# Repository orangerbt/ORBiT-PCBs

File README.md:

# ORBiT Avionics

Schematics and PCBS for ORBiT Avionics system.

## Modules

- Telemetry (GPS, IMU, atmospheric conditions, remote control)
    - Digi 9Xtend 900MHz 1W radio
    - Linx TM series GNSS reciever
    - Bosch BMX055 IMU
    - Bosch BME280 atmospheric conditions sensor
- Power (battery management, charging, regulation)
    - TI bq40z60 BMU
    - TI TPS40305 5V regulator
- Actuation (power devices)
    - 3x Microchip MCP23008 I2C I/O expanders
    - 2x Microchip MCP33926 H-bridge drivers
- Data acquisition (sensors)
    - Analog Devices AD9201 ADC
    - Analog Devices LTC2984 temperature measurement system

## Notes
- Make sure to power down HDMI framer via I2C0
- Add CAT24C256 EEPROMs to identify modules via I2C2
- Ensure I2C pins have pull-ups
- Add power sequencing to all boards
- Data acquisition to be based on PRUDAQ
- Add LTC2983/4/6 and LTC6904 to DAQ
- Test points

## Hardware pin mapping

### Telemetry

- UART4 - P8 33 uart4_rtsn, 35 uart4_ctsn, P9 11 uart4_rxd, 13 uart4_txd
- UART5 - P8 37 uart5_txd, 38 uart5_rxd
- SPI0  - P8 26-28, P9 17 spi0_cs0, 18 spi0_d1, 21 spi0_d0, 22 spi0_sclk
    - SPI0 addressing
    - P8 26 gpio61 = A0
    - P8 27 gpio86 = A1
    - P8 28 gpio88 = A2
- I2C1  - P9 24 I2C1_SCL, 26 I2C1_SDA
- I2C2  - P9 19 I2C2_SCL, 22 I2C2_SDA

### Power management

- I2C1 - P9 24 I2C1_SCL, 26 I2C1_SDA

### Actuator control

- I2C1 - P9 24 I2C1_SCL, 26 I2C1_SDA
- GPIO - P9 25, 27, 28

### PRUDAQ:
- P8 27-30, 39-46
- P9 25-31

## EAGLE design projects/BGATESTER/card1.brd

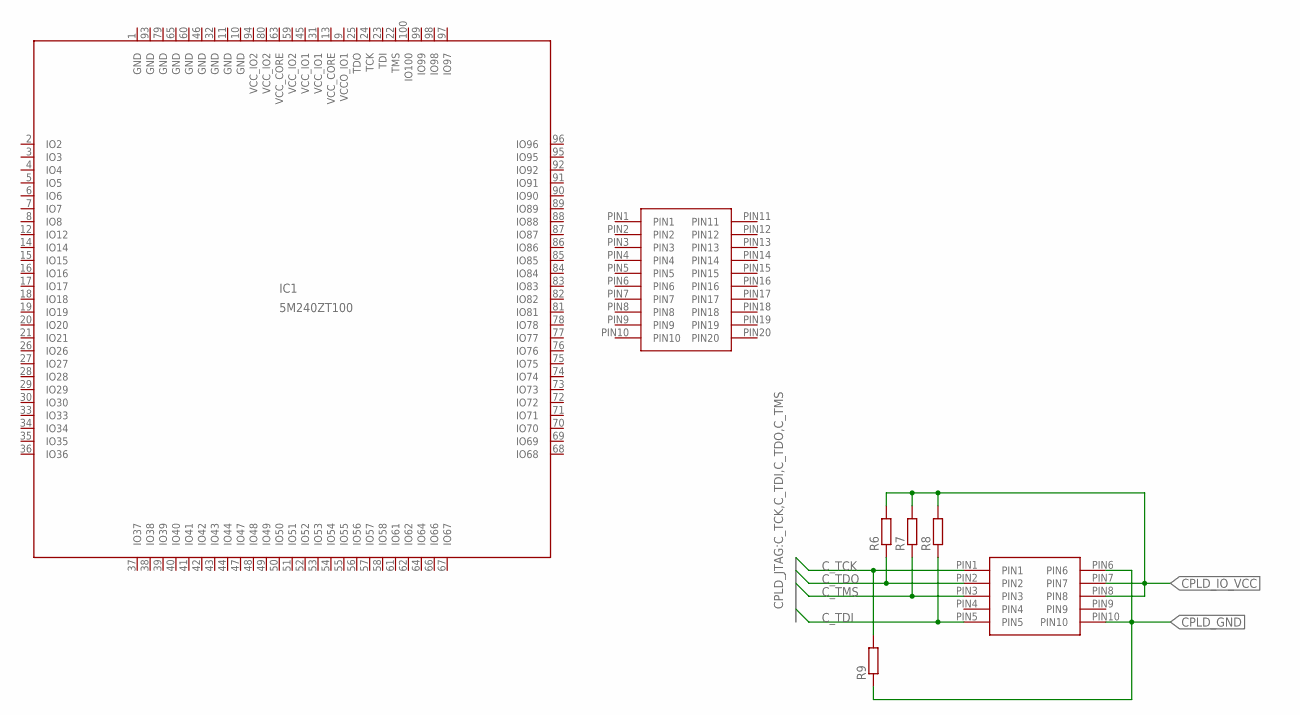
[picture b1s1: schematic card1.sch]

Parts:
IC1: 5M240ZT100; TQFP100
R6, R7, R8, R9: R-EU_R2012; R2012
U$1: 10PIN10PIN_BOARD; 10PIN_BOARD
U$3: CONN-10PINR/A-10PIN; R/A-10PIN

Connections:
CPLD_GND: R9.1, U$3.PIN6, U$3.PIN10
CPLD_IO_VCC: R6.2, R7.2, R8.2, U$3.PIN7, U$3.PIN8
C_TCK: R9.2, U$3.PIN1
C_TDI: R8.1, U$3.PIN5
C_TDO: R6.1, U$3.PIN2
C_TMS: R7.1, U$3.PIN3
GND: IC1.1 (GND), IC1.10 (GND), IC1.11 (GND), IC1.32 (GND), IC1.46 (GND), IC1.60 (GND), IC1.65 (GND), IC1.79 (GND), IC1.93 (GND)
VCCO_IO1: IC1.9 (VCCO_IO1)
VCC_CORE: IC1.13 (VCC_CORE), IC1.63 (VCC_CORE)
VCC_IO1: IC1.31 (VCC_IO1), IC1.45 (VCC_IO1)
VCC_IO2: IC1.59 (VCC_IO2), IC1.80 (VCC_IO2), IC1.94 (VCC_IO2)

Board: 2 copper layers, 7 parts (0 on the bottom side), 10 nets, no tracks yet.

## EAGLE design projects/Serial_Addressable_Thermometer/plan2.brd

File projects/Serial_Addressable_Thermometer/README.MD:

# Serial Addressable Thermometer
## Plan 3
- Use PIC micro controller with AD, use I2C as communication
- Adventage: faster, build in assembly
- Disadventage: Hard to upgrade
## Part List
    1. FPC connector
       1. 68611014422
       2. https://www.digikey.com/product-detail/en/wurth-electronics-inc/68611014422/732-1996-1-ND/2060620
       3. AFFC-100-10-051-11
       4. https://www.digikey.com/product-detail/en/assmann-wsw-components/AFFC-100-10-051-11/AE11354-ND/6570435
    2. NTC resistor 0805
       1. B57471V2103J062
       2. https://www.digikey.com/product-detail/en/epcos-tdk/B57471V2103J062/495-7449-1-ND/6073141
    3. 10K resistor 0805
       1. RMCF0805JT10K0
       2. https://www.digikey.com/product-detail/en/stackpole-electronics-inc/RMCF0805JT10K0/RMCF0805JT10K0CT-ND/1942577
    4. CAP CER 47UF 6.3V X5R 0805
       1. JMK212BBJ476MG-T
       2. https://www.digikey.com/product-detail/en/taiyo-yuden/JMK212BBJ476MG-T/587-4280-1-ND/5344315
    5. PIC16F18424-I/ST-ND
       1. A/D 11x12b; D/A 1x5b
       2. https://www.digikey.com/product-detail/en/microchip-technology/PIC16F18424-I-ST/PIC16F18424-I-ST-ND/8639243
    6. S4B-ZR-SM4A-TF(LF)(SN)
       1. CONN HEADER SMD R/A 4POS 1.5MM
       2. https://www.digikey.com/product-detail/en/jst-sales-america-inc/S4B-ZR-SM4A-TF-LF-SN/455-1695-1-ND/926822
    7. CONN SOCKET 26-28AWG CRIMP TIN
       1. https://www.digikey.com/product-detail/en/jst-sales-america-inc/SZH-002T-P0.5/455-1130-1-ND/527362
    8. CONN HOUSING ZH 4POS 1.5MM WHT
       1. https://www.digikey.com/product-detail/en/jst-sales-america-inc/ZHR-4/455-1202-ND/608643
    9. CONN HEADER SMD R/A 6POS 1.5MM
       1.  https://www.digikey.com/product-detail/en/jst-sales-america-inc/S6B-ZR-SM4A-TF-LF-SN/455-1610-1-ND/858041
    10. CONN HOUSING ZH 6POS 1.5MM	COPY 
        1.  https://www.digikey.com/product-detail/en/jst-sales-america-inc/ZHR-6/455-1129-ND/527361

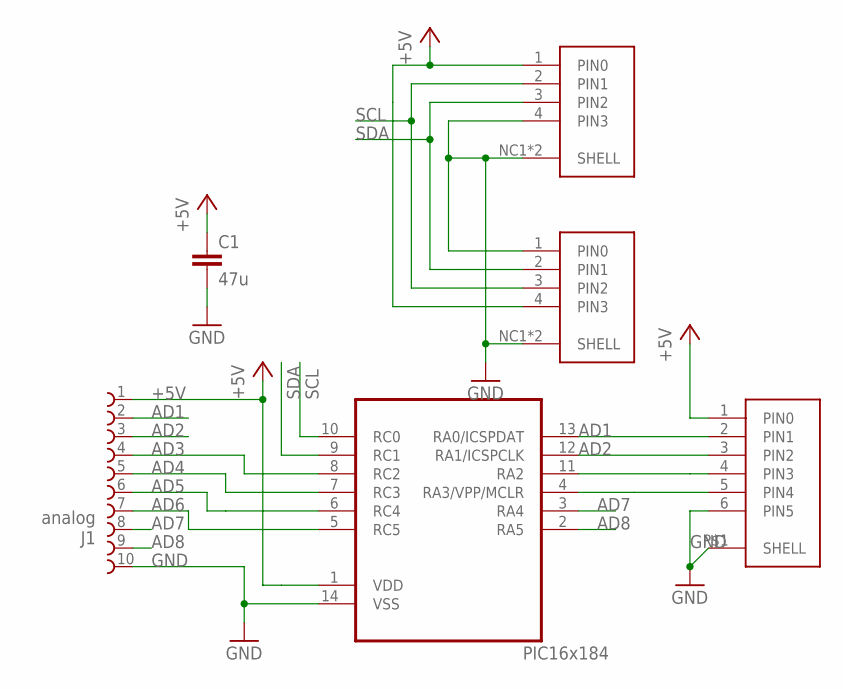
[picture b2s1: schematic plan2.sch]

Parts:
C1: 47u; C0805
J1: analog; 68611014422
MAINCON: PIC16F18424; 14-TSSOP
U$2: IIC1; JST_ZH_4PIN
U$3: IIC2; JST_ZH_4PIN
U$4: programming; JST_ZH_6PIN

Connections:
+5V: C1.1, J1.1 (10), MAINCON.1 (VDD), U$2.1 (PIN0), U$3.4 (PIN3), U$4.1 (PIN0)
AD1: J1.2 (9), MAINCON.13 (RA0/ICSPDAT), U$4.2 (PIN1)
AD2: J1.3 (8), MAINCON.12 (RA1/ICSPCLK), U$4.3 (PIN2)
AD3: J1.4 (7), MAINCON.8 (RC2)
AD4: J1.5 (6), MAINCON.7 (RC3)
AD5: J1.6 (5), MAINCON.6 (RC4)
AD6: J1.7 (4), MAINCON.5 (RC5)
AD7: J1.8 (3), MAINCON.3 (RA4)
AD8: J1.9 (2), MAINCON.2 (RA5)
GND: C1.2, J1.10 (1), MAINCON.14 (VSS), U$2.4 (PIN3), U$2.NC1 (SHELL), U$2.NC2 (SHELL), U$3.1 (PIN0), U$3.NC1 (SHELL), U$3.NC2 (SHELL), U$4.6 (PIN5), U$4.P$1 (SHELL)
unnamed: MAINCON.11 (RA2), U$4.4 (PIN3)
unnamed: MAINCON.4 (RA3/VPP/MCLR), U$4.5 (PIN4)
SCL: MAINCON.10 (RC0), U$2.2 (PIN1), U$3.3 (PIN2)
SDA: MAINCON.9 (RC1), U$2.3 (PIN2), U$3.2 (PIN1)

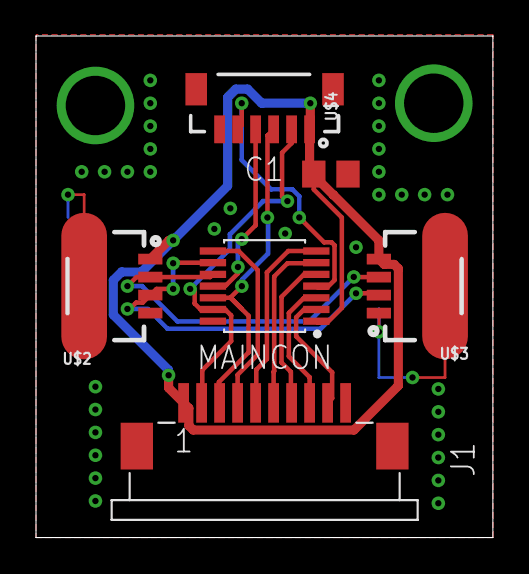
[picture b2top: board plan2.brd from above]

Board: 2 copper layers, 25.4 x 27.9 mm, 6 parts (0 on the bottom side), 14 nets.

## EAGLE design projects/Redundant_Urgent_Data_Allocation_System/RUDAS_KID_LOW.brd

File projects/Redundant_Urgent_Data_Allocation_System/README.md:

# Chip Selection
1.  Low-end board Chip
    1.  STM32F103VGT6
        1.  https://www.digikey.com/product-detail/en/stmicroelectronics/STM32F103VGT6/497-11120-ND/2529309
2.  High-end board Chip
    1.  STM32F412VET6
        1.  https://www.digikey.com/product-detail/en/stmicroelectronics/STM32F412VET6/497-17837-ND/6621744
3.  Dual Port SRAM
    1.  71V30S55TFG
        1.  https://www.digikey.com/product-detail/en/idt-integrated-device-technology-inc/71V30S55TFG/800-3622-ND/4400847
4.  CPLD
    1.  5M240ZT100C5N
        1.  https://www.digikey.com/product-detail/en/intel/5M240ZT100C5N/544-2716-ND/2499439
5.  CAN Driver
    1.  ISO1050
    2.  https://www.digikey.com/product-detail/en/texas-instruments/ISO1050DUBR/296-24818-1-ND/2094658
6.  Voltage Regulator
    1.  AP1501A-12K5G-13
        1.  https://www.digikey.com/product-detail/en/diodes-incorporated/AP1501A-12K5G-13/AP1501A-12K5G-13DIDKR-ND/8546155
    2.  LM2679SX-3.3/NOPB
        1.  https://www.digikey.com/product-detail/en/texas-instruments/LM2679SX-3.3-NOPB/LM2679SX-3.3-NOPBCT-ND/3526908
    3.  AP1509-50SG-13
        1.  https://www.digikey.com/product-detail/en/diodes-incorporated/AP1509-50SG-13/AP1509-50SGDICT-ND/1301653

# Connector
1. JTAG
   1. 3M 2500
      1. 20 Pin
         1. https://www.digikey.com/product-detail/en/3m/N2520-6002-RB/MHC20K-ND/755179
         2. https://www.digikey.com/product-detail/en/3m/N2520-5002-RB/MHE20K-ND/755191
         3. https://www.digikey.com/product-detail/en/3m/N2520-6V0C-RB-WE/MSH20KCT-ND/1125449
2. FPC
   1. Wurth Electronics Inc. WR-FPC
      1. https://www.digikey.com/products/en/connectors-interconnects/ffc-fpc-flat-flexible-connectors/399?k=&pkeyword=&sv=0&sf=0&FV=ffe0018f%2Cfffc02dc&quantity=1&ColumnSort=0&page=1&stock=1&datasheet=1&photo=1&pageSize=25

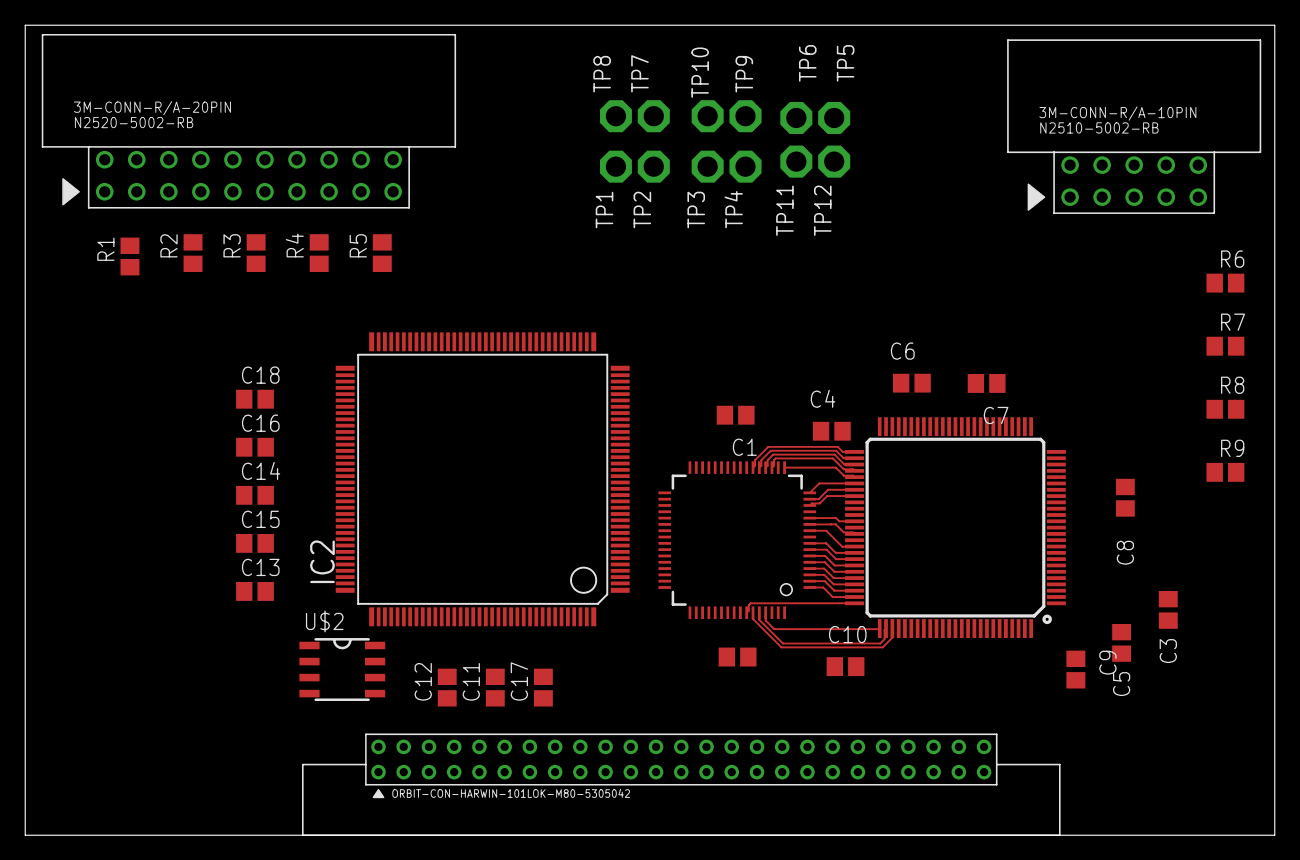
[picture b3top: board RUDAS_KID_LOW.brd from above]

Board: 4 copper layers, 99.0 x 64.2 mm, 46 parts (0 on the bottom side), 102 nets.

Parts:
C1, C2, C3, C4, C5, C6, C7, C8, C9, C10, C11, C12, C13, C14, C15, C16, C17, C18: C2012
IC2: STM32F103VGT6; LQFP144
IC3: 5M240ZT100; TQFP100
R1, R2, R3, R4, R5, R6, R7, R8, R9: R2012
TP1, TP2, TP3, TP4, TP5, TP6, TP7, TP8, TP9, TP10, TP11, TP12: TP063; TP_063
U$1: IDT71V30; TQFP64
U$2: ISO1050; SOP8
U$3: CONN-10PINR/A-10PIN; R/A-10PIN
U$4: CONN-20PINR/A-20PIN; R/A-20PIN
U$5: CARD_EDGE_50PINM80-5305042; M80-5305042

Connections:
!BUSY!: IC3.77, U$1.60
!CE!: IC3.75, U$1.58
!INT!: IC3.76, U$1.61
!OE!: IC3.74, U$1.1
A0: IC3.73, U$1.2
A1: IC3.72, U$1.3
A2: IC3.71, U$1.4
A3: IC3.70, U$1.5
A4: IC3.69, U$1.6
A5: IC3.68, U$1.7
A6: IC3.67, U$1.8
A7: IC3.66, U$1.10
A8: IC3.64, U$1.11
A9: IC3.62, U$1.12
CAN_H_P: U$2.7, U$5.PIN4
CAN_L_P: U$2.6, U$5.PIN5
CPLD_GND: C3.2, C4.2, C5.2, C6.2, C7.2, C8.2, C9.2, C10.2, IC3.1, IC3.10, IC3.11, IC3.32, IC3.46, IC3.60, IC3.65, IC3.79, IC3.93, R9.1, U$3.PIN6, U$3.PIN10
CPLD_IO_VCC: R6.2, R7.2, R8.2, U$3.PIN7, U$3.PIN8
CPLD_VCC: C3.1, C4.1, C5.1, C6.1, C7.1, C8.1, C9.1, C10.1
CPLD_VCC_CORE: IC3.13, IC3.63
CPLD_VCC_IO2: IC3.59, IC3.80, IC3.94
CPL_VCC_IO1: IC3.9, IC3.31, IC3.45
C_TCK: IC3.24, R9.2, U$3.PIN1
C_TDI: IC3.23, R8.1, U$3.PIN5
C_TDO: IC3.25, R6.1, U$3.PIN2
C_TMS: IC3.22, R7.1, U$3.PIN3
D0: IC3.58, U$1.14
D1: IC3.57, U$1.15
D2: IC3.56, U$1.16
D3: IC3.55, U$1.17
D4: IC3.54, U$1.19
D5: IC3.53, U$1.20
D6: IC3.52, U$1.21
D7: IC3.51, U$1.22
FSMC_!NE1!: IC2.123, U$1.55
FSMC_!NOE!: IC2.118, U$1.48
FSMC_A0: IC2.10, U$1.47
FSMC_A1: IC2.11, U$1.46
FSMC_A2: IC2.12, U$1.45
FSMC_A3: IC2.13, U$1.44
FSMC_A4: IC2.14, U$1.43
FSMC_A5: IC2.15, U$1.42
FSMC_A6: IC2.50, U$1.41
FSMC_A7: IC2.53, U$1.39
FSMC_A8: IC2.54, U$1.38
FSMC_A9: IC2.55, U$1.37
FSMC_D0: IC2.85, U$1.26
FSMC_D1: IC2.86, U$1.27
FSMC_D2: IC2.114, U$1.28
FSMC_D3: IC2.115, U$1.29
FSMC_D4: IC2.58, U$1.31
FSMC_D5: IC2.59, U$1.32
FSMC_D6: IC2.60, U$1.33
FSMC_D7: IC2.63, U$1.34
LAN_CLK_N0: IC3.81, U$5.PIN9
LAN_CLK_N1: IC3.85, U$5.PIN15
LAN_CLK_N2: IC3.96, U$5.PIN21
LAN_CLK_N3: IC3.29, U$5.PIN34
LAN_CLK_N4: IC3.19, U$5.PIN40
LAN_CLK_N5: IC3.5, U$5.PIN46
LAN_CLK_P0: IC3.82, U$5.PIN10
LAN_CLK_P1: IC3.86, U$5.PIN16
LAN_CLK_P2: IC3.97, U$5.PIN22
LAN_CLK_P3: IC3.28, U$5.PIN35
LAN_CLK_P4: IC3.18, U$5.PIN41
LAN_CLK_P5: IC3.4, U$5.PIN47
LAN_N0: IC3.83, U$5.PIN11
LAN_N1: IC3.87, U$5.PIN17
LAN_N2: IC3.98, U$5.PIN23
LAN_N3: IC3.27, U$5.PIN36
LAN_N4: IC3.17, U$5.PIN42
LAN_N5: IC3.3, U$5.PIN48
LAN_P0: IC3.84, U$5.PIN12
LAN_P1: IC3.88, U$5.PIN18
LAN_P2: IC3.99, U$5.PIN24
LAN_P3: IC3.26, U$5.PIN37
LAN_P4: IC3.16, U$5.PIN43
LAN_P5: IC3.2, U$5.PIN49
unnamed: C1.1, C2.1, U$1.56, U$1.57
unnamed: C1.2, C2.2, U$1.24, U$1.25
R/!W!: IC3.78, U$1.59
SIGNAL_GND: U$2.5, U$5.PIN8, U$5.PIN14, U$5.PIN20, U$5.PIN33, U$5.PIN39, U$5.PIN45
STM32_CAN_RX: IC2.103, TP7.TP, U$2.2
STM32_CAN_TX: IC2.104, TP8.TP, U$2.3
STM32_I2C1_SCL: IC2.136, TP9.TP
STM32_I2C1_SDA: IC2.137, TP10.TP
STM32_SPI1_CS: IC2.40, TP1.TP
STM32_SPI1_MISO: IC2.42, TP3.TP
STM32_SPI1_MOSI: IC2.43, TP4.TP
STM32_SPI1_SCK: IC2.41, TP2.TP
STM32_UART1_RX: IC2.102, TP6.TP
STM32_UART1_TX: IC2.101, TP5.TP
STM32_UART2_RX: IC2.36, TP12.TP
STM32_UART2_TX: IC2.35, TP11.TP
S_GND: C11.2, C12.2, C13.2, C14.2, C15.2, C16.2, C17.2, C18.2, IC2.16, IC2.38, IC2.51, IC2.61, IC2.71, IC2.83, IC2.94, IC2.107, IC2.120, IC2.130, IC2.143, R5.1, U$2.4, U$4.PIN12, U$4.PIN13, U$4.PIN14, U$4.PIN15, U$4.PIN16, U$4.PIN17, U$4.PIN18, U$4.PIN19, U$4.PIN20
S_RST: IC2.25, U$4.PIN9
S_TCK: IC2.109, R5.2, U$4.PIN5
S_TDI: IC2.110, R2.1, U$4.PIN3
S_TDO: IC2.133, R4.1, U$4.PIN7
S_TMS: IC2.105, R3.1, U$4.PIN4
S_TRST: IC2.134, R1.1, U$4.PIN2
S_VCC: C11.1, C12.1, C13.1, C14.1, C15.1, C16.1, C17.1, C18.1, IC2.17, IC2.39, IC2.52, IC2.62, IC2.72, IC2.84, IC2.95, IC2.108, IC2.121, IC2.131, IC2.144, R1.2, R2.2, R3.2, R4.2, U$2.1, U$4.PIN1, U$4.PIN11

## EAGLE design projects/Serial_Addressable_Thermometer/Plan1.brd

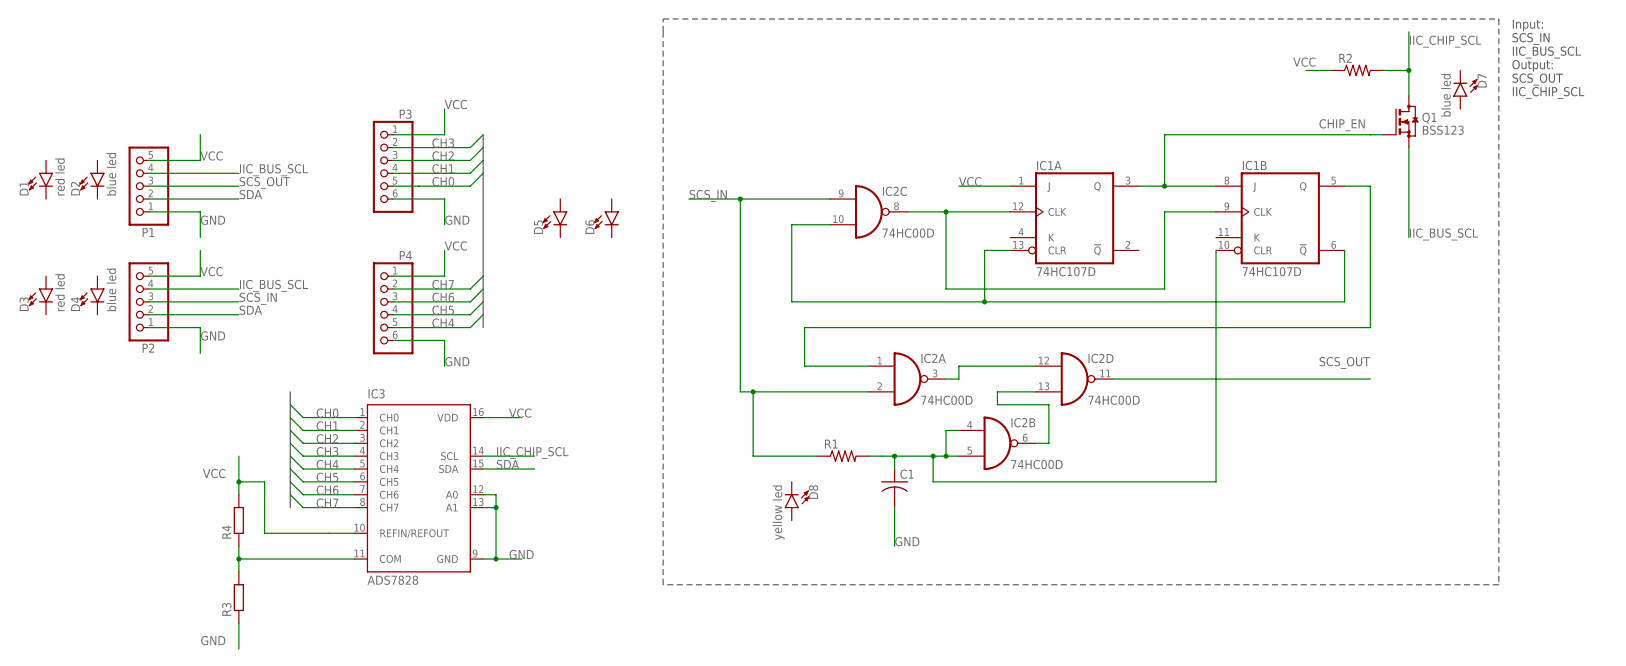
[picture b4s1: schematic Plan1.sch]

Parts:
C1: C-USC1206; C1206
D1, D3: red led; LED-0603
D2, D4, D7: blue led; LED-0603
D5, D6: LED0603; LED-0603
D8: yellow led; LED-0603
IC1: 74HC107D; SO14
IC2: 74HC00D; SO14
IC3: ADS7828; TSSOP16-PW
P1, P2: 105313-05; 105313-**05
P3, P4: 105313-06; 105313-**06
Q1: BSS123; SOT23
R1, R2: R-US_R1206; R1206
R3, R4: R-EU_R2012; R2012

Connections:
CH0: IC3.1 (CH0), P3.5
CH1: IC3.2 (CH1), P3.4
CH2: IC3.3 (CH2), P3.3
CH3: IC3.4 (CH3), P3.2
CH4: IC3.5 (CH4), P4.5
CH5: IC3.6 (CH5), P4.4
CH6: IC3.7 (CH6), P4.3
CH7: IC3.8 (CH7), P4.2
CHIP_EN: IC1.3 (Q), IC1.8 (J), Q1.1 (G)
GND: C1.2, IC1.7 (GND), IC2.7 (GND), IC3.9 (GND), IC3.12 (A0), IC3.13 (A1), P1.1, P2.1, P3.6, P4.6, R3.1
IIC_BUS_SCL: P1.4, P2.4, Q1.2 (S)
IIC_CHIP_SCL: IC3.14 (SCL), Q1.3 (D), R2.2
unnamed: IC1.9 (CLK), IC1.12 (CLK), IC2.8 (O)
unnamed: C1.1, IC1.10 (CLR), IC2.4 (I0), IC2.5 (I1), R1.2
unnamed: IC2.6 (O), IC2.13 (I1)
unnamed: IC1.6 (!Q), IC1.13 (CLR), IC2.10 (I1)
unnamed: IC1.5 (Q), IC2.1 (I0)
unnamed: IC2.3 (O), IC2.12 (I0)
unnamed: IC3.11 (COM), R3.2, R4.1
SCS_IN: IC2.2 (I1), IC2.9 (I0), P2.3, R1.1
SCS_OUT: IC2.11 (O), P1.3
SDA: IC3.15 (SDA), P1.2, P2.2
VCC: IC1.1 (J), IC1.14 (VCC), IC2.14 (VCC), IC3.10 (REFIN/REFOUT), IC3.16 (VDD), P1.5, P2.5, P3.1, P4.1, R2.1, R4.2

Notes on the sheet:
Input: SCS_IN IIC_BUS_SCL Output: SCS_OUT IIC_CHIP_SCL

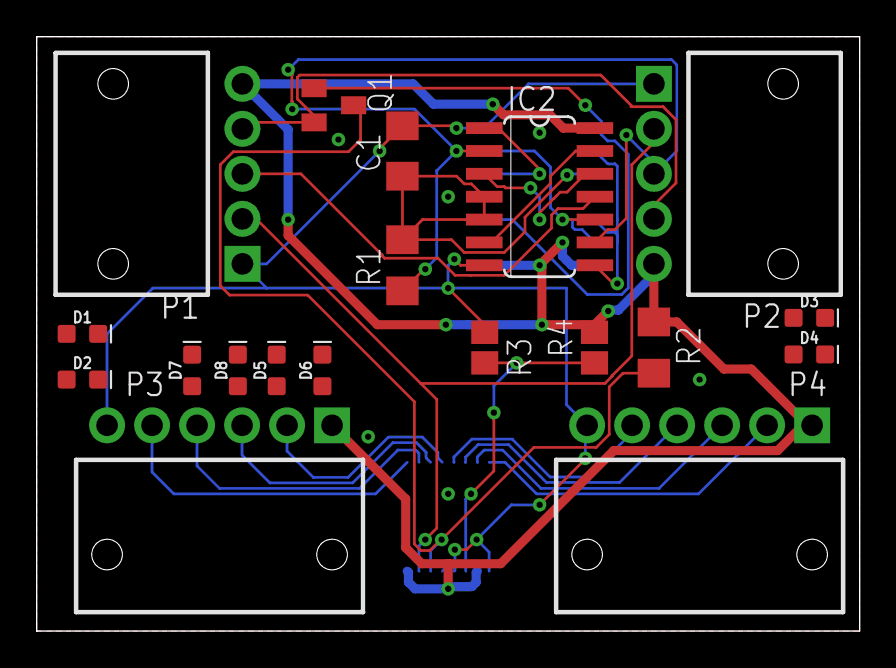
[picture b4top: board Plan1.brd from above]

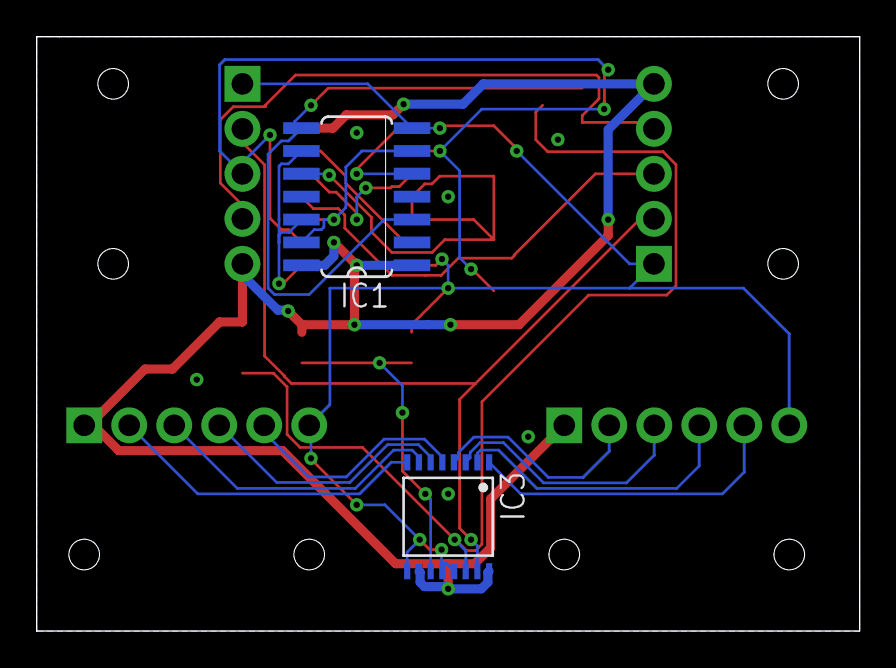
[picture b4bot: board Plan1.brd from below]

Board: 2 copper layers, 45.7 x 33.0 mm, 21 parts (2 on the bottom side), 23 nets.

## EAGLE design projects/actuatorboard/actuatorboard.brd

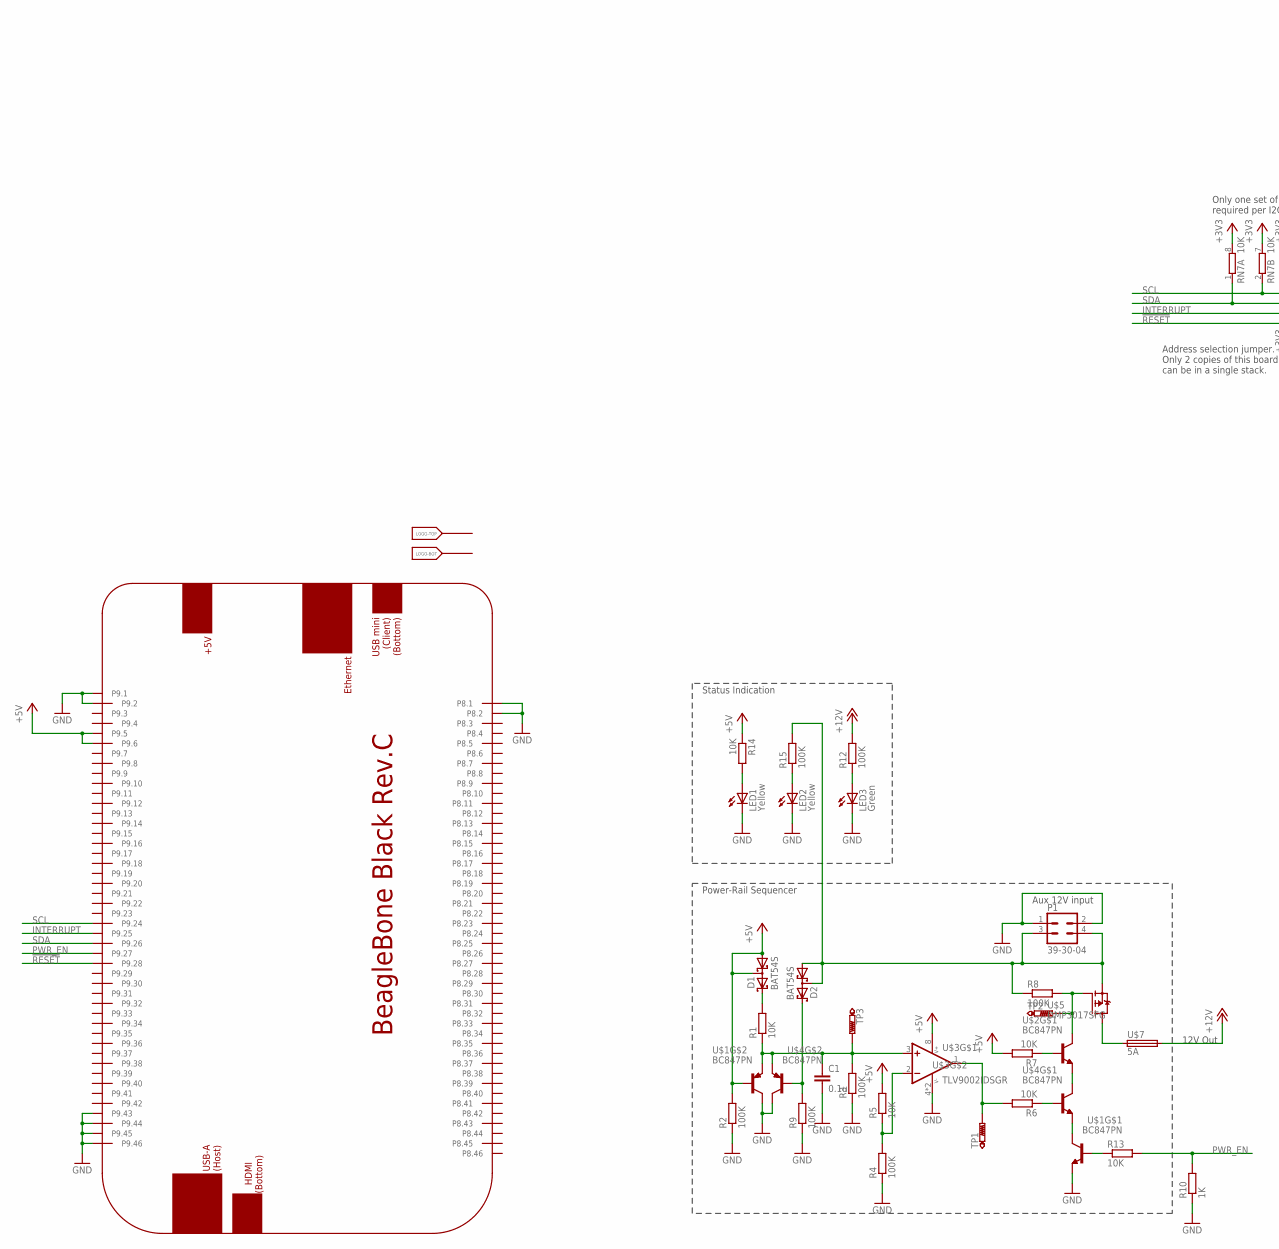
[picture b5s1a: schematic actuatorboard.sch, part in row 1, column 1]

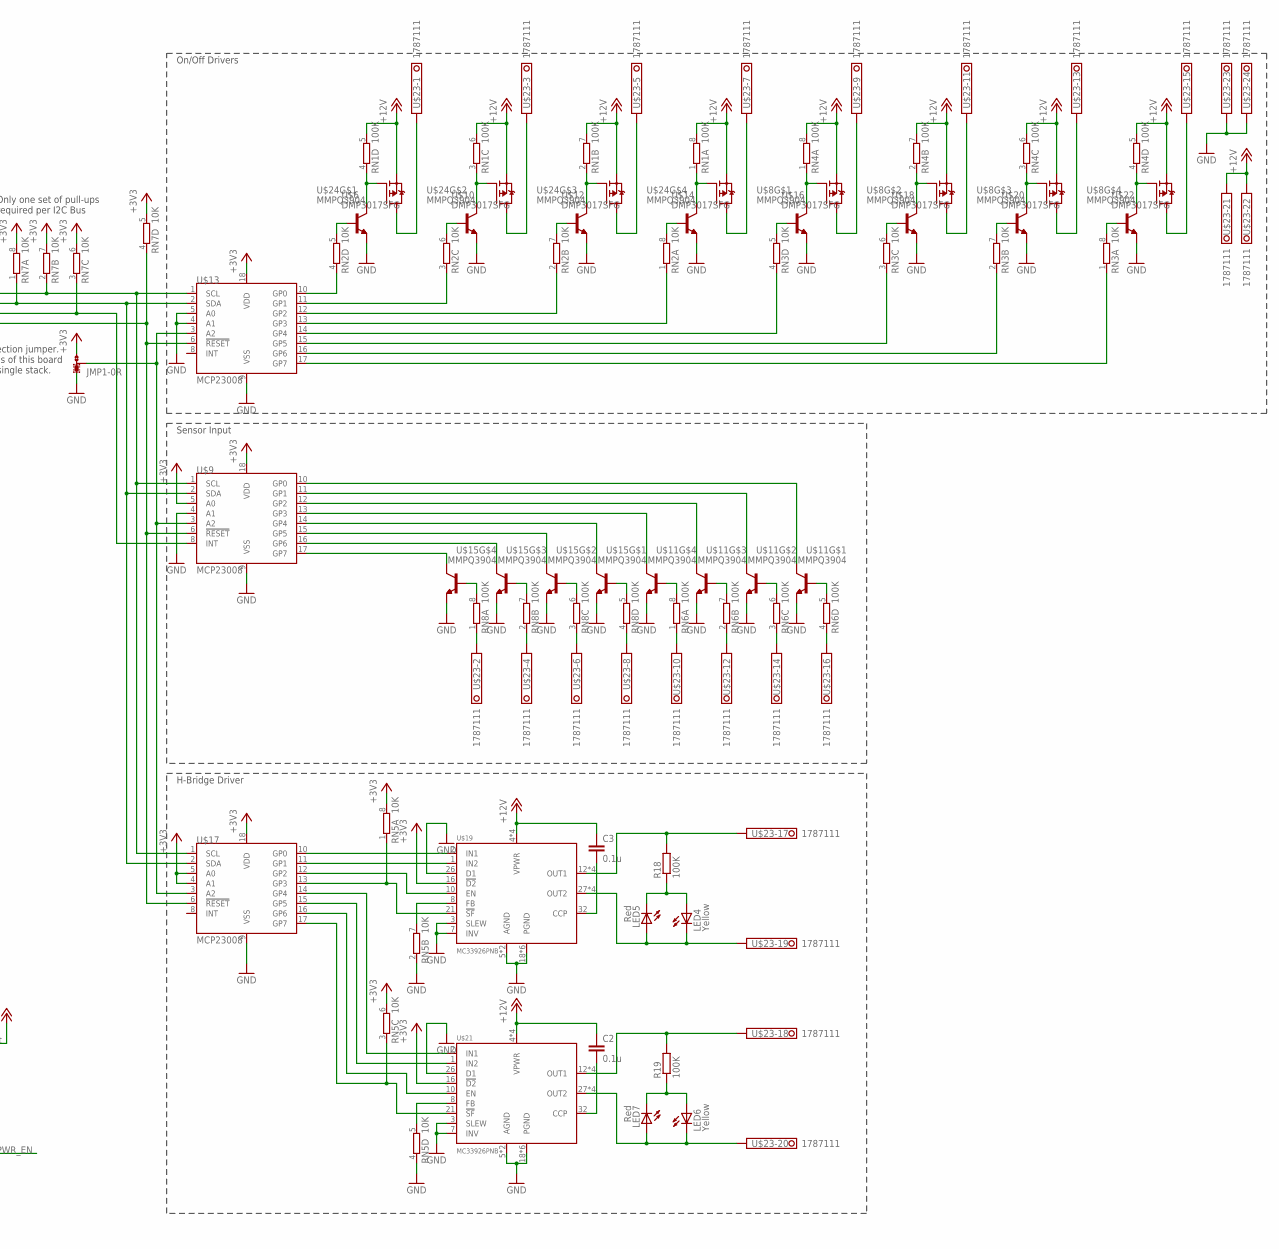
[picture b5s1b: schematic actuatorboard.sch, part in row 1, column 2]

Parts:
C1, C2, C3: 0.1u; C0805
D1, D2: BAT54S; SOT23
JMP1: 0R-JUMPA; A0R-JMP
LED1, LED2, LED4, LED6: Yellow; CHIPLED_0805
LED3: Green; CHIPLED_0805
LED5, LED7: Red; CHIPLED_0805
LOGO: SU_LOGO-DUMMY; SU_LOGO_DS
P1: 39-30-04; 39-30-?04?
PCB1: BEAGLEBONE_BLACK_CAPENO_ETH; BEAGLEBONE_BLACK_CAPE_NO_ETH
R1, R5, R6, R7, R13, R14: 10K; R0805
R2, R3, R4, R8, R9, R12, R15, R18, R19: 100K; R0805
R10: 1K; R0805
RN1, RN4, RN6, RN8: 100K; EXBV8V
RN2, RN3, RN5, RN7: 10K; EXBV8V
TP1, TP2, TP3: PTR1B1,27; B1,27
U$1, U$2, U$4: BC847PN; SOT363-INFINION
U$3: TLV9002IDSGR; S-PWSON-N8
U$5, U$6, U$10, U$12, U$14, U$16, U$18, U$20, U$22: DMP3017SFG; POWERDI3333-8
U$7: 5A; SMD-1206
U$8, U$11, U$15, U$24: MMPQ3904; SOIC-16
U$9, U$13, U$17: MCP23008; SO-18W
U$19, U$21: MC33926PNB; PQFN-32
U$23: 1787111

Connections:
!RESET!: PCB1.P9.28, RN7.4 (1), U$9.6 (!RESET!), U$13.6 (!RESET!), U$17.6 (!RESET!)
+3V3: JMP1.3, RN5.6 (2), RN5.8 (2), RN7.5 (2), RN7.6 (2), RN7.7 (2), RN7.8 (2), U$9.5 (A0), U$9.18 (VDD), U$13.18 (VDD), U$17.4 (A1), U$17.5 (A0), U$17.18 (VDD), U$19.16 (!D2!), U$21.16 (!D2!)
+5V: D1.1 (A1), D1.3 (C1A2), PCB1.P9.5, PCB1.P9.6, R2.2, R5.2, R7.2, R14.1, U$1.5 (B), U$3.8 (V+)
+12V: C2.1, C3.1, R12.2, RN1.5 (2), RN1.6 (2), RN1.7 (2), RN1.8 (2), RN4.5 (2), RN4.6 (2), RN4.7 (2), RN4.8 (2), U$6.P$1 (S), U$6.P$2 (S), U$6.P$3 (S), U$7.2, U$10.P$1 (S), U$10.P$2 (S), U$10.P$3 (S), U$12.P$1 (S), U$12.P$2 (S), U$12.P$3 (S), U$14.P$1 (S), U$14.P$2 (S), U$14.P$3 (S), U$16.P$1 (S), U$16.P$2 (S), U$16.P$3 (S), U$18.P$1 (S), U$18.P$2 (S), U$18.P$3 (S), U$19.4 (VPWR), U$19.6 (VPWR), U$19.11 (VPWR), U$19.31 (VPWR), U$20.P$1 (S), U$20.P$2 (S), U$20.P$3 (S), U$21.4 (VPWR), U$21.6 (VPWR), U$21.11 (VPWR), U$21.31 (VPWR), U$22.P$1 (S), U$22.P$2 (S), U$22.P$3 (S), U$23.21, U$23.22
GND: C1.2, JMP1.1, LED1.C, LED2.C, LED3.C, P1.1, P1.2, PCB1.P8.1, PCB1.P8.2, PCB1.P9.1, PCB1.P9.2, PCB1.P9.43, PCB1.P9.44, PCB1.P9.45, PCB1.P9.46, R2.1, R3.1, R4.1, R9.1, R10.1, RN5.2 (1), RN5.4 (1), U$1.1 (E), U$1.3 (C), U$3.4 (V-), U$3.PAD (V-), U$4.3 (C), U$8.P$10 (E), U$8.P$12 (E), U$8.P$14 (E), U$8.P$16 (E), U$9.4 (A1), U$9.9 (VSS), U$11.P$10 (E), U$11.P$12 (E), U$11.P$14 (E), U$11.P$16 (E), U$13.4 (A1), U$13.5 (A0), U$13.9 (VSS), U$15.P$10 (E), U$15.P$12 (E), U$15.P$14 (E), U$15.P$16 (E), U$17.9 (VSS), U$19.3 (SLEW), U$19.5 (AGND), U$19.7 (INV), U$19.18 (PGND), U$19.19 (PGND), U$19.20 (PGND), U$19.22 (PGND), U$19.23 (PGND), U$19.24 (PGND), U$19.26 (D1), U$19.PAD (AGND), U$21.3 (SLEW), U$21.5 (AGND), U$21.7 (INV), U$21.18 (PGND), U$21.19 (PGND), U$21.20 (PGND), U$21.22 (PGND), U$21.23 (PGND), U$21.24 (PGND), U$21.26 (D1), U$21.PAD (AGND), U$23.23, U$23.24, U$24.P$10 (E), U$24.P$12 (E), U$24.P$14 (E), U$24.P$16 (E)
INTERRUPT: PCB1.P9.25, RN7.3 (1), U$9.8 (INT)
unnamed: D2.2 (C2), R9.2, U$4.5 (B)
unnamed: C1.1, R1.1, R3.2, TP3.TP, U$1.4 (E), U$3.3 (+IN), U$4.4 (E)
unnamed: R4.2, R5.1, U$3.2 (-IN)
unnamed: U$1.6 (C), U$4.1 (E)
unnamed: R6.1, U$4.2 (B)
unnamed: R6.2, TP1.TP, U$3.1 (OUT)
unnamed: U$2.1 (E), U$4.6 (C)
unnamed: U$5.P$5 (D), U$5.P$6 (D), U$5.P$7 (D), U$5.P$8 (D), U$7.1
unnamed: R7.1, U$2.2 (B)
unnamed: D1.2 (C2), R1.2
unnamed: U$6.P$5 (D), U$6.P$6 (D), U$6.P$7 (D), U$6.P$8 (D), U$23.1
unnamed: D2.1 (A1), D2.3 (C1A2), P1.3, P1.4, R8.1, R15.2, U$5.P$1 (S), U$5.P$2 (S), U$5.P$3 (S)
unnamed: R8.2, TP2.TP, U$2.6 (C), U$5.P$4 (G)
unnamed: R13.1, U$1.2 (B)
unnamed: RN1.4 (1), U$6.P$4 (G), U$24.P$1 (C), U$24.P$2 (C)
unnamed: RN2.4 (1), U$13.10 (GP0)
unnamed: RN2.5 (2), U$24.P$15 (B)
unnamed: U$17.10 (GP0), U$19.2 (IN1)
unnamed: U$17.11 (GP1), U$19.1 (IN2)
unnamed: LED1.A, R14.2
unnamed: LED2.A, R15.1
unnamed: LED3.A, R12.1
unnamed: U$10.P$5 (D), U$10.P$6 (D), U$10.P$7 (D), U$10.P$8 (D), U$23.3
unnamed: RN1.3 (1), U$10.P$4 (G), U$24.P$3 (C), U$24.P$4 (C)
unnamed: RN2.6 (2), U$24.P$13 (B)
unnamed: RN2.3 (1), U$13.11 (GP1)
unnamed: U$12.P$5 (D), U$12.P$6 (D), U$12.P$7 (D), U$12.P$8 (D), U$23.5
unnamed: RN1.2 (1), U$12.P$4 (G), U$24.P$5 (C), U$24.P$6 (C)
unnamed: RN2.7 (2), U$24.P$11 (B)
unnamed: RN2.2 (1), U$13.12 (GP2)
unnamed: U$14.P$5 (D), U$14.P$6 (D), U$14.P$7 (D), U$14.P$8 (D), U$23.7
unnamed: RN1.1, U$14.P$4 (G), U$24.P$7 (C), U$24.P$8 (C)
unnamed: RN2.8 (2), U$24.P$9 (B)
unnamed: RN2.1, U$13.13 (GP3)
unnamed: U$17.12 (GP2), U$19.10 (EN)
unnamed: RN6.2 (1), U$23.12
unnamed: U$16.P$5 (D), U$16.P$6 (D), U$16.P$7 (D), U$16.P$8 (D), U$23.9
unnamed: RN4.1, U$8.P$1 (C), U$8.P$2 (C), U$16.P$4 (G)
unnamed: RN3.5 (2), U$8.P$15 (B)
unnamed: RN3.4 (1), U$13.14 (GP4)
unnamed: U$18.P$5 (D), U$18.P$6 (D), U$18.P$7 (D), U$18.P$8 (D), U$23.11
unnamed: RN4.2 (1), U$8.P$3 (C), U$8.P$4 (C), U$18.P$4 (G)
unnamed: RN3.6 (2), U$8.P$13 (B)
unnamed: RN3.3 (1), U$13.15 (GP5)
unnamed: U$20.P$5 (D), U$20.P$6 (D), U$20.P$7 (D), U$20.P$8 (D), U$23.13
unnamed: RN4.3 (1), U$8.P$5 (C), U$8.P$6 (C), U$20.P$4 (G)
unnamed: RN3.7 (2), U$8.P$11 (B)
unnamed: RN3.2 (1), U$13.16 (GP6)
unnamed: U$22.P$5 (D), U$22.P$6 (D), U$22.P$7 (D), U$22.P$8 (D), U$23.15
unnamed: RN4.4 (1), U$8.P$7 (C), U$8.P$8 (C), U$22.P$4 (G)
unnamed: RN3.8 (2), U$8.P$9 (B)
unnamed: RN3.1, U$13.17 (GP7)
unnamed: U$9.10 (GP0), U$11.P$1 (C), U$11.P$2 (C)
unnamed: U$9.11 (GP1), U$11.P$3 (C), U$11.P$4 (C)
unnamed: RN6.5 (2), U$11.P$15 (B)
unnamed: U$9.12 (GP2), U$11.P$5 (C), U$11.P$6 (C)
unnamed: U$9.13 (GP3), U$11.P$7 (C), U$11.P$8 (C)
unnamed: U$9.14 (GP4), U$15.P$1 (C), U$15.P$2 (C)
unnamed: U$9.15 (GP5), U$15.P$3 (C), U$15.P$4 (C)
unnamed: U$9.16 (GP6), U$15.P$5 (C), U$15.P$6 (C)
unnamed: U$9.17 (GP7), U$15.P$7 (C), U$15.P$8 (C)
unnamed: RN6.6 (2), U$11.P$13 (B)
unnamed: RN6.7 (2), U$11.P$11 (B)
unnamed: RN6.8 (2), U$11.P$9 (B)
unnamed: RN8.5 (2), U$15.P$15 (B)
unnamed: RN5.1, U$17.13 (GP3), U$19.21 (!SF!)
unnamed: RN5.7 (2), U$19.8 (FB)
unnamed: U$17.14 (GP4), U$21.2 (IN1)
unnamed: U$17.15 (GP5), U$21.1 (IN2)
unnamed: RN8.6 (2), U$15.P$13 (B)
unnamed: RN8.7 (2), U$15.P$11 (B)
unnamed: RN8.8 (2), U$15.P$9 (B)
unnamed: U$17.16 (GP6), U$21.10 (EN)
unnamed: RN5.3 (1), U$17.17 (GP7), U$21.21 (!SF!)
unnamed: RN5.5 (2), U$21.8 (FB)
unnamed: LED4.A, LED5.C, R18.1
unnamed: LED4.C, LED5.A, U$19.27 (OUT2), U$19.28 (OUT2), U$19.29 (OUT2), U$19.30 (OUT2), U$23.19
unnamed: RN8.1, U$23.2
unnamed: R18.2, U$19.12 (OUT1), U$19.13 (OUT1), U$19.14 (OUT1), U$19.15 (OUT1), U$23.17
unnamed: LED6.A, LED7.C, R19.1
unnamed: LED6.C, LED7.A, U$21.27 (OUT2), U$21.28 (OUT2), U$21.29 (OUT2), U$21.30 (OUT2), U$23.20
unnamed: R19.2, U$21.12 (OUT1), U$21.13 (OUT1), U$21.14 (OUT1), U$21.15 (OUT1), U$23.18
unnamed: C2.2, U$21.32 (CCP)
unnamed: C3.2, U$19.32 (CCP)
unnamed: RN8.2 (1), U$23.4
unnamed: RN8.3 (1), U$23.6
unnamed: RN8.4 (1), U$23.8
unnamed: RN6.1, U$23.10
unnamed: RN6.3 (1), U$23.14
unnamed: RN6.4 (1), U$23.16
unnamed: JMP1.2, U$9.3 (A2), U$13.3 (A2), U$17.3 (A2)
PWR_EN: PCB1.P9.27, R10.2, R13.2
SCL: PCB1.P9.24, RN7.2 (1), U$9.1 (SCL), U$13.1 (SCL), U$17.1 (SCL)
SDA: PCB1.P9.26, RN7.1, U$9.2 (SDA), U$13.2 (SDA), U$17.2 (SDA)

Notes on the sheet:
Aux 12V input
Power-Rail Sequencer
12V Out
Only one set of pull-ups required per I2C Bus
Status Indication
On/Off Drivers
Sensor Input
H-Bridge Driver
Address selection jumper. Only 2 copies of this board can be in a single stack.

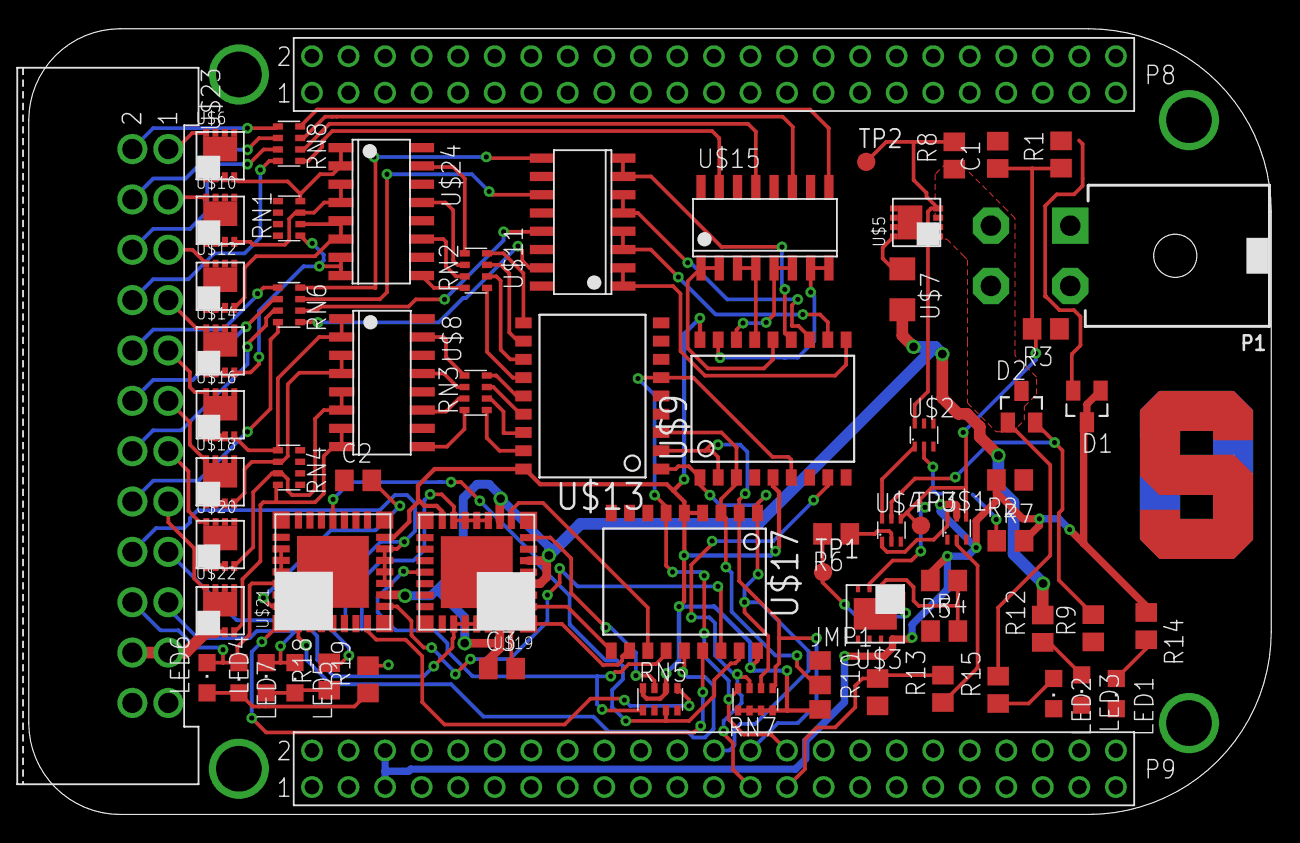
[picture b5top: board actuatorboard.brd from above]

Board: 2 copper layers, 86.4 x 54.6 mm, 67 parts (0 on the bottom side), 100 nets.

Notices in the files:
parts and their libraries:
Wurth_Elektronik_Electromechanic_FPC_Con: Copyright: Würth Elektronik
SparkFun-LED: Licensing: Creative Commons ShareAlike 4.0 International - https://creativecommons.org/licenses/by-sa/4.0
con-molex-mini-fit: Copyright (C) 2011, Bob Starr
